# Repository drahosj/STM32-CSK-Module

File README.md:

STM32-CSK-Module
================

STM32 based processor board for the CubeSat kit motherboard

Uses the Aerodyne Labs KiCad library https://github.com/aerodynelabs/kicadlib

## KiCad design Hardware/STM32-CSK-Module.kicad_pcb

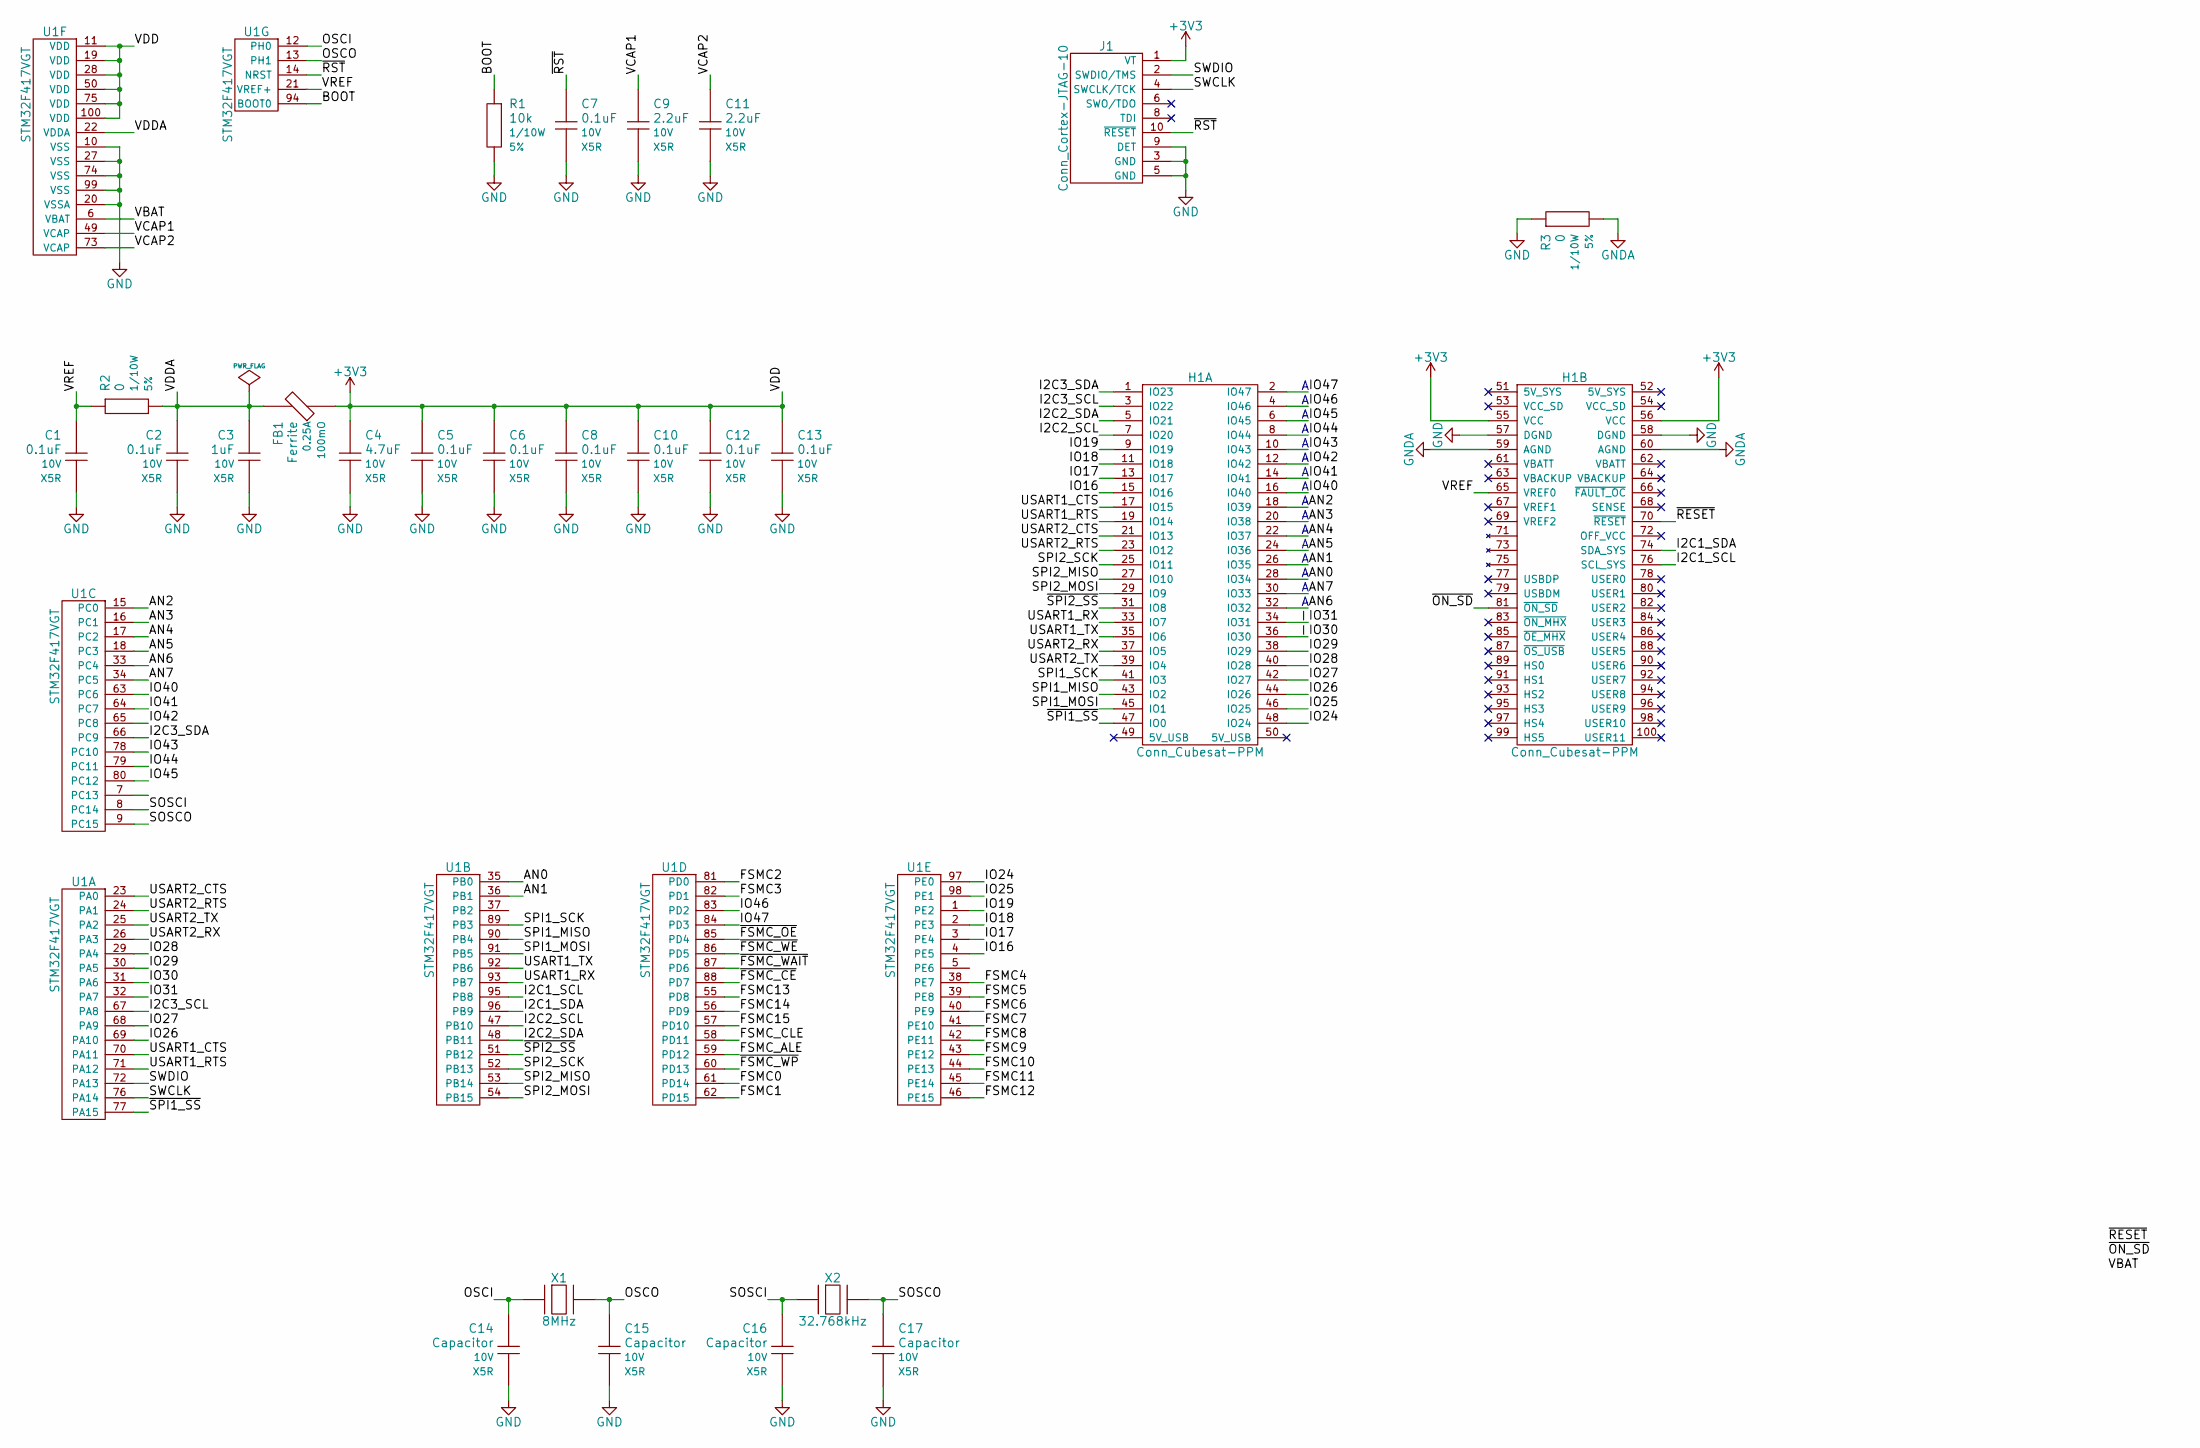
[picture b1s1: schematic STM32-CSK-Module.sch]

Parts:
C1, C2, C5, C6, C7, C8, C10, C12, C13: 0.1uF; CAPC1608N; Voltage 10V; Manufacturer Part # Value
C3: 1uF; CAPC1608N; Voltage 10V; Manufacturer Part # Value
C4: 4.7uF; CAPC1608N; Voltage 10V; Manufacturer Part # Value
C9, C11: 2.2uF; CAPC1608N; Voltage 10V; Manufacturer Part # Value
C14, C15, C16, C17: Capacitor; CAPC1608N; Voltage 10V; Manufacturer Part # Value
FB1: Ferrite; INDC1608N; Manufacturer Part # Value
H1: Conn_Cubesat-PPM
J1: Conn_Cortex-JTAG-10; Conn_Samtec-FTSH-105-D-RA-K
R1: 10k; RESC1608N; Tolerance 5%; Manufacturer Part # Value
R2, R3: 0; RESC1608N; Tolerance 5%; Manufacturer Part # Value
U1: STM32F417VGT; QFP50P1600X1600-100N
X1: 8MHz; Crystal_Abracon-ABM3
X2: 32.768kHz; Crystal_Abracon-ABS06

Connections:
+3V3: C4.1, C5.1, C6.1, C8.1, C10.1, C12.1, C13.1, FB1.2, H1.55 (VCC), H1.56 (VCC), J1.1 (VT), U1.11 (VDD), U1.19 (VDD), U1.28 (VDD), U1.50 (VDD), U1.75 (VDD), U1.100 (VDD)
/AN0: H1.28 (IO34), U1.35 (PB0)
/AN1: H1.26 (IO35), U1.36 (PB1)
/AN2: H1.18 (IO39), U1.15 (PC0)
/AN3: H1.20 (IO38), U1.16 (PC1)
/AN4: H1.22 (IO37), U1.17 (PC2)
/AN5: H1.24 (IO36), U1.18 (PC3)
/AN6: H1.32 (IO32), U1.33 (PC4)
/AN7: H1.30 (IO33), U1.34 (PC5)
/BOOT: R1.1, U1.94 (BOOT0)
/FSMC0: U1.61 (PD14)
/FSMC1: U1.62 (PD15)
/FSMC2: U1.81 (PD0)
/FSMC3: U1.82 (PD1)
/FSMC4: U1.38 (PE7)
/FSMC5: U1.39 (PE8)
/FSMC6: U1.40 (PE9)
/FSMC7: U1.41 (PE10)
/FSMC8: U1.42 (PE11)
/FSMC9: U1.43 (PE12)
/FSMC10: U1.44 (PE13)
/FSMC11: U1.45 (PE14)
/FSMC12: U1.46 (PE15)
/FSMC13: U1.55 (PD8)
/FSMC14: U1.56 (PD9)
/FSMC15: U1.57 (PD10)
/FSMC_ALE: U1.59 (PD12)
/FSMC_CLE: U1.58 (PD11)
/I2C1_SCL: H1.76 (SCL_SYS), U1.95 (PB8)
/I2C1_SDA: H1.74 (SDA_SYS), U1.96 (PB9)
/I2C2_SCL: H1.7 (IO20), U1.47 (PB10)
/I2C2_SDA: H1.5 (IO21), U1.48 (PB11)
/I2C3_SCL: H1.3 (IO22), U1.67 (PA8)
/I2C3_SDA: H1.1 (IO23), U1.66 (PC9)
/IO16: H1.15 (IO16), U1.4 (PE5)
/IO17: H1.13 (IO17), U1.3 (PE4)
/IO18: H1.11 (IO18), U1.2 (PE3)
/IO19: H1.9 (IO19), U1.1 (PE2)
/IO24: H1.48 (IO24), U1.97 (PE0)
/IO25: H1.46 (IO25), U1.98 (PE1)
/IO26: H1.44 (IO26), U1.69 (PA10)
/IO27: H1.42 (IO27), U1.68 (PA9)
/IO28: H1.40 (IO28), U1.29 (PA4)
/IO29: H1.38 (IO29), U1.30 (PA5)
/IO30: H1.36 (IO30), U1.31 (PA6)
/IO31: H1.34 (IO31), U1.32 (PA7)
/IO40: H1.16 (IO40), U1.63 (PC6)
/IO41: H1.14 (IO41), U1.64 (PC7)
/IO42: H1.12 (IO42), U1.65 (PC8)
/IO43: H1.10 (IO43), U1.78 (PC10)
/IO44: H1.8 (IO44), U1.79 (PC11)
/IO45: H1.6 (IO45), U1.80 (PC12)
/IO46: H1.4 (IO46), U1.83 (PD2)
/IO47: H1.2 (IO47), U1.84 (PD3)
/OSCI: C14.1, U1.12 (PH0), X1.1
/OSCO: C15.1, U1.13 (PH1), X1.2
/SOSCI: C16.1, U1.8 (PC14), X2.1
/SOSCO: C17.1, U1.9 (PC15), X2.2
/SPI1_MISO: H1.43 (IO2), U1.90 (PB4)
/SPI1_MOSI: H1.45 (IO1), U1.91 (PB5)
/SPI1_SCK: H1.41 (IO3), U1.89 (PB3)
/SPI2_MISO: H1.27 (IO10), U1.53 (PB14)
/SPI2_MOSI: H1.29 (IO9), U1.54 (PB15)
/SPI2_SCK: H1.25 (IO11), U1.52 (PB13)
/SWCLK: J1.4 (SWCLK/TCK), U1.76 (PA14)
/SWDIO: J1.2 (SWDIO/TMS), U1.72 (PA13)
/USART1_CTS: H1.17 (IO15), U1.70 (PA11)
/USART1_RTS: H1.19 (IO14), U1.71 (PA12)
/USART1_RX: H1.33 (IO7), U1.93 (PB7)
/USART1_TX: H1.35 (IO6), U1.92 (PB6)
/USART2_CTS: H1.21 (IO13), U1.23 (PA0)
/USART2_RTS: H1.23 (IO12), U1.24 (PA1)
/USART2_RX: H1.37 (IO5), U1.26 (PA3)
/USART2_TX: H1.39 (IO4), U1.25 (PA2)
/VBAT: U1.6 (VBAT)
/VCAP1: C9.1, U1.49 (VCAP)
/VCAP2: C11.1, U1.73 (VCAP)
/VDDA: C2.1, C3.1, FB1.1, R2.2, U1.22 (VDDA)
/VREF: C1.1, H1.65 (VREF0), R2.1, U1.21 (VREF+)
/~FSMC_CE: U1.88 (PD7)
/~FSMC_OE: U1.85 (PD4)
/~FSMC_WAIT: U1.87 (PD6)
/~FSMC_WE: U1.86 (PD5)
/~FSMC_WP: U1.60 (PD13)
/~ON_SD: H1.81 (~ON_SD)
/~RESET: H1.70 (~RESET)
/~RST: C7.1, J1.10 (~RESET), U1.14 (NRST)
/~SPI1_SS: H1.47 (IO0), U1.77 (PA15)
/~SPI2_SS: H1.31 (IO8), U1.51 (PB12)
GND: C1.2, C2.2, C3.2, C4.2, C5.2, C6.2, C7.2, C8.2, C9.2, C10.2, C11.2, C12.2, C13.2, C14.2, C15.2, C16.2, C17.2, H1.57 (DGND), H1.58 (DGND), J1.3 (GND), J1.5 (GND), J1.9 (DET), R1.2, R3.1, U1.10 (VSS), U1.20 (VSSA), U1.27 (VSS), U1.74 (VSS), U1.99 (VSS)
GNDA: H1.59 (AGND), H1.60 (AGND), R3.2

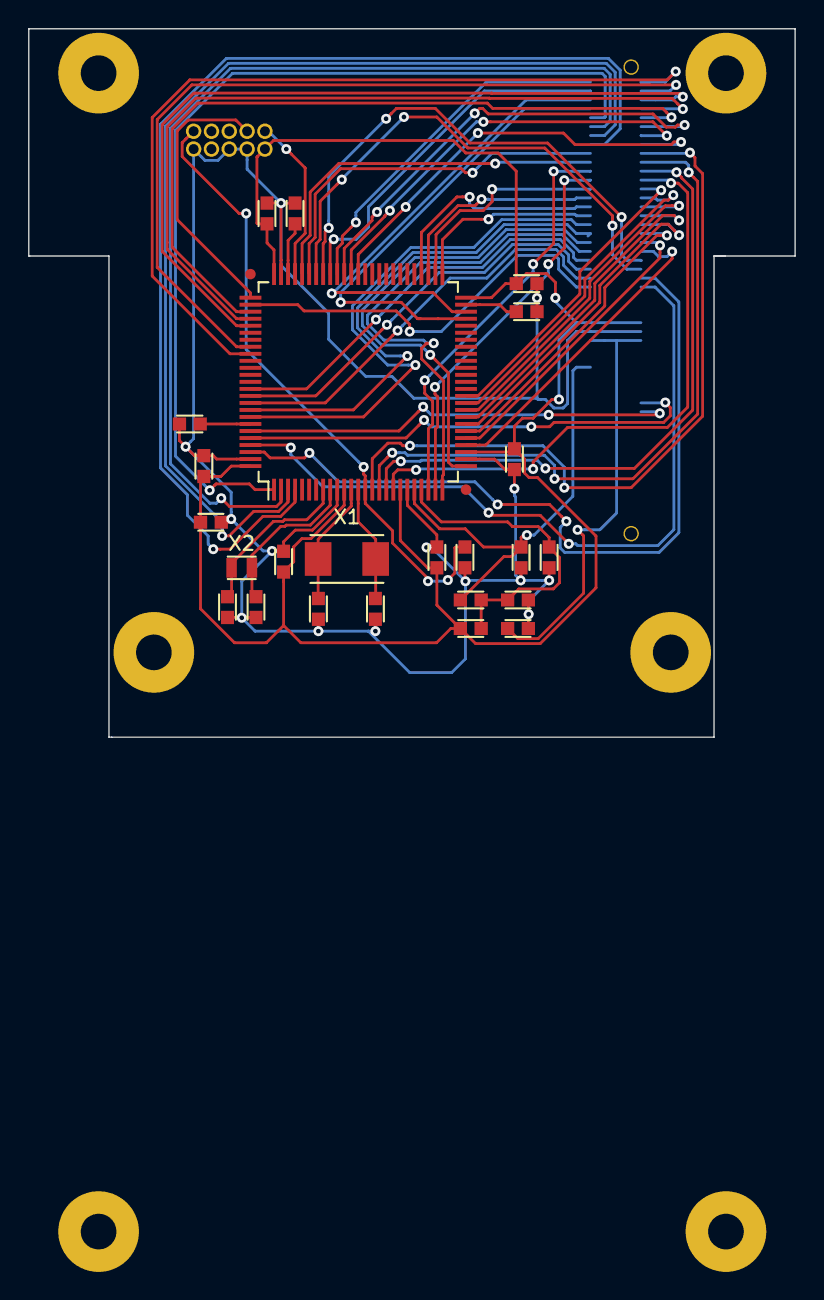
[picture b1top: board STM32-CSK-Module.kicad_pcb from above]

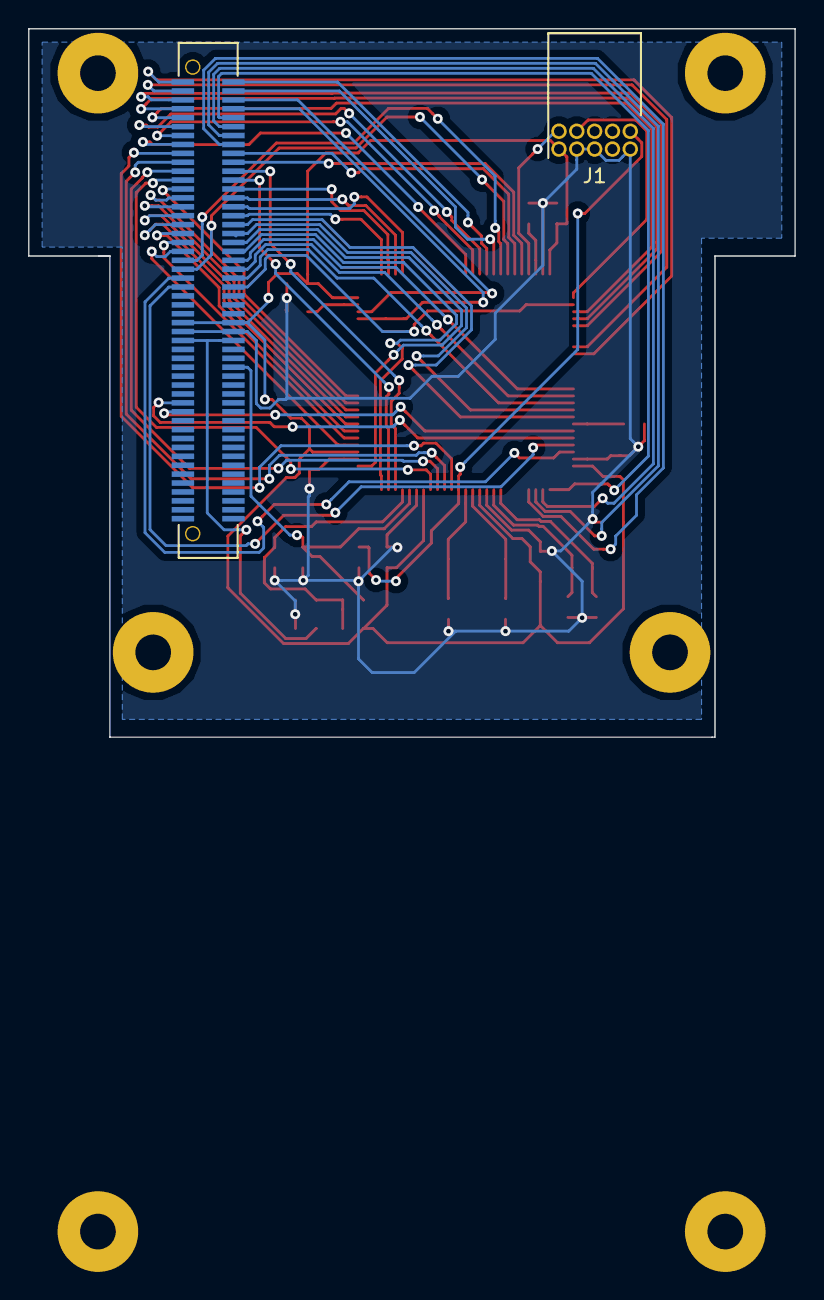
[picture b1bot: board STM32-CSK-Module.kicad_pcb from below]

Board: 2 copper layers, 54.6 x 50.5 mm, 32 parts (2 on the bottom side), 65 nets.

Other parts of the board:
MECH-HOLE220, MECH-HOLE220#2, MECH-HOLE220#3, MECH-HOLE220#4, MECH-HOLE220#5, MECH-HOLE220#6: VAL**; MTGP575H254

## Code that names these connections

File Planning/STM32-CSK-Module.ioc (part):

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Mcu.Name=STM32F417V(E-G)Tx
Mcu.Package=LQFP100
Mcu.UserName=STM32F417VGTx
PA0-WKUP.Mode=CTS_RTS
PA0-WKUP.Signal=USART2_CTS
PA1.Mode=CTS_RTS
PA1.Signal=USART2_RTS
PA11.Mode=CTS_RTS
PA11.Signal=USART1_CTS
PA12.Mode=CTS_RTS
PA12.Signal=USART1_RTS
PA13.Mode=Serial-Wire
PA13.Signal=SYS_JTMS-SWDIO
PA14.Mode=Serial-Wire
PA14.Signal=SYS_JTCK-SWCLK
PA15.Mode=NSS_Signal_Hard
PA15.Signal=SPI1_NSS
PA2.Mode=Asynchronous
PA2.Signal=USART2_TX
PA3.Mode=Asynchronous
PA3.Signal=USART2_RX
PA4.Signal=COMP_DAC1_group
PA5.Signal=COMP_DAC2_group
PA8.Mode=I2C
PA8.Signal=I2C3_SCL
PB10.Mode=I2C
PB10.Signal=I2C2_SCL
PB11.Mode=I2C
PB11.Signal=I2C2_SDA
PB12.Mode=NSS_Signal_Hard
PB12.Signal=SPI2_NSS
PB13.Mode=Full_Duplex_Master
PB13.Signal=SPI2_SCK
PB14.Mode=Full_Duplex_Master
PB14.Signal=SPI2_MISO
PB15.Mode=Full_Duplex_Master
PB15.Signal=SPI2_MOSI
PB3.Mode=Full_Duplex_Master
PB3.Signal=SPI1_SCK
PB4.Mode=Full_Duplex_Master
PB4.Signal=SPI1_MISO
PB5.Mode=Full_Duplex_Master
PB5.Signal=SPI1_MOSI
PB6.Mode=Asynchronous
PB6.Signal=USART1_TX
PB7.Mode=Asynchronous
PB7.Signal=USART1_RX
PB8.Mode=I2C
PB8.Signal=I2C1_SCL
PB9.Mode=I2C
PB9.Signal=I2C1_SDA
PC14-OSC32_IN.Mode=LSE-External-Oscillator
PC14-OSC32_IN.Signal=RCC_OSC32_IN
PC15-OSC32_OUT.Mode=LSE-External-Oscillator
PC15-OSC32_OUT.Signal=RCC_OSC32_OUT
PC9.Mode=I2C
PC9.Signal=I2C3_SDA
PD0.Signal=FSMC_D2_DA2
PD1.Signal=FSMC_D3_DA3
PD10.Signal=FSMC_D15_DA15
PD11.Signal=FSMC_A16_CLE
PD12.Signal=FSMC_A17_ALE
PD14.Signal=FSMC_D0_DA0
PD15.Signal=FSMC_D1_DA1
PD4.Signal=FSMC_NOE
PD5.Signal=FSMC_NWE
PD6.Signal=FSMC_NWAIT
PD7.Mode=NandChipSelect2_1
PD7.Signal=FSMC_NCE2
PD8.Signal=FSMC_D13_DA13
PD9.Signal=FSMC_D14_DA14
PE10.Signal=FSMC_D7_DA7
PE11.Signal=FSMC_D8_DA8
PE12.Signal=FSMC_D9_DA9
PE13.Signal=FSMC_D10_DA10
PE14.Signal=FSMC_D11_DA11
PE15.Signal=FSMC_D12_DA12
PE7.Signal=FSMC_D4_DA4
PE8.Signal=FSMC_D5_DA5
PE9.Signal=FSMC_D6_DA6
PH0-OSC_IN.Mode=HSE-External-Oscillator
PH0-OSC_IN.Signal=RCC_OSC_IN
PH1-OSC_OUT.Mode=HSE-External-Oscillator
PH1-OSC_OUT.Signal=RCC_OSC_OUT
RCC.HSE_VALUE=25000000

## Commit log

2014-12-02 KiCad project
2014-12-02 Physical interface layout
2014-12-02 Annotation
2014-12-05 Add MCU
2014-12-22 Migrate to new KiCad
2014-12-22 Add crystals and programmer
2015-01-14 Add flash
2015-01-15 Add PPM target datasheet
2015-01-15 Peripheral pin mapping
2015-01-15 Add STM32Cube project
2015-01-15 Peripheral PPM connections
2015-01-20 Update PPM numbering
2015-03-01 Began routing without external flash
2015-03-01 Routed all essentials
    All "essential" IO routed, and all power/misc routed as well.
2015-03-02 Progress on routing flexible GPIOs
    About 50%
2015-03-02 Finished all H1 GPIO
2015-03-02 Done. Moderately clean.
    All used pins routed.
2015-03-02 Created ground plane
    Large parts of ground plane unconnected. Not surprising given the density
    of traces in most parts.
2015-03-03 FUCK FUCKING FUCK FUCK FUCK FUCK FUCKING FUCK FUCK
    COCK
2015-03-06 Restarted with the connector NOT FUCKING WRONG!
2015-03-06 Done routing it properly
